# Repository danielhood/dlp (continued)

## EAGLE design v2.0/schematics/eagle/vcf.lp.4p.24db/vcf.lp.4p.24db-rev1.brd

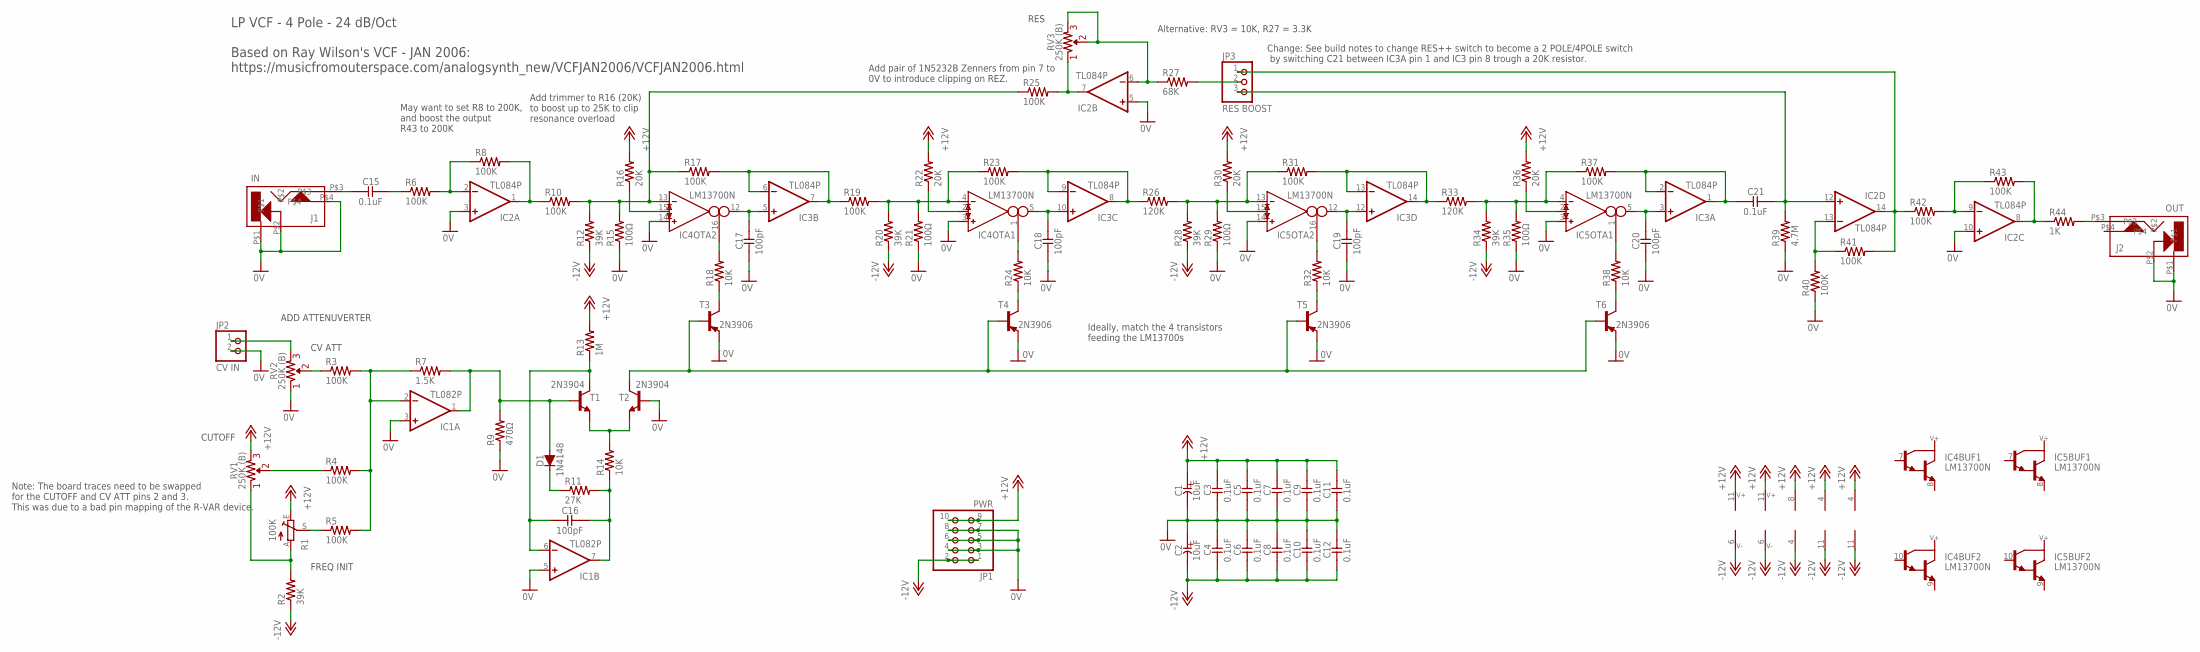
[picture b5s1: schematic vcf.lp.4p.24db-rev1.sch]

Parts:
C1, C2: 10uF; E2-5
C3, C4, C5, C6, C7, C8, C9, C10, C11, C12, C15, C21: 0.1uF; C025-024X044
C16, C17, C18, C19, C20: 100pF; C025-024X044
D1: 1N4148; DO35-7
IC1: TL082P; DIL08
IC2, IC3: TL084P; DIL14
IC4, IC5: LM13700N; DIL16
J1: IN; CL1384
J2: OUT; CL1384
JP1: PWR; 2X05
JP2: CV IN; 1X02
JP3: RES BOOST; 1X03
R1: 100K; CA6V
R2, R12, R20, R28, R34: 39K; 0207/7
R3, R4, R5, R6, R8, R10, R17, R19, R23, R25, R31, R37, R40, R41, R42, R43: 100K; 0207/7
R7: 1.5K; 0207/7
R9: 470Ω; 0207/7
R11: 27K; 0207/7
R13: 1M; 0207/7
R14, R18, R24, R32, R38: 10K; 0207/7
R15, R21, R29, R35: 100Ω; 0207/7
R16, R22, R30, R36: 20K; 0207/7
R26, R33: 120K; 0207/7
R27: 68K; 0207/7
R39: 4.7M; 0207/7
R44: 1K; 0207/7
RV1, RV2, RV3: 250K (B); _COMMON_3RP/1610N
T1, T2: 2N3904; TO92-EBC
T3, T4, T5, T6: 2N3906; TO92-EBC

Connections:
0V: C1.-, C2.+, C3.2, C4.1, C5.2, C6.1, C7.2, C8.1, C9.2, C10.1, C11.2, C12.1, C17.2, C18.2, C19.2, C20.2, IC1.3 (+IN), IC1.5 (+IN), IC2.3 (+IN), IC2.5 (+IN), IC2.10 (+IN), IC4.3 (IN_P), IC4.14 (IN_P), IC5.3 (IN_P), IC5.14 (IN_P), J1.P$1, J1.P$2, J1.P$4, J2.P$1, J2.P$2, JP1.3, JP1.4, JP1.5, JP1.6, JP1.7, JP1.8, JP2.2, R9.1, R15.1, R21.1, R29.1, R35.1, R39.1, R40.1, RV2.1, T2.B, T3.E, T4.E, T5.E, T6.E
+12V: C1.+, C3.1, C5.1, C7.1, C9.1, C11.1, IC1.8 (V+), IC2.4 (V+), IC3.4 (V+), IC4.11 (V+), IC5.11 (V+), JP1.9, JP1.10, R1.E, R13.2, R16.2, R22.2, R30.2, R36.2, RV1.2
-12V: C2.-, C4.2, C6.2, C8.2, C10.2, C12.2, IC1.4 (V-), IC2.11 (V-), IC3.11 (V-), IC4.6 (V-), IC5.6 (V-), JP1.1, JP1.2, R2.1, R12.1, R20.1, R28.1, R34.1
unnamed: R1.A, R2.2, RV1.1
unnamed: R4.1, RV1.3
unnamed: JP2.1, RV2.2
unnamed: R1.S, R5.1
unnamed: IC1.2 (-IN), R3.2, R4.2, R5.2, R7.1
unnamed: D1.A, IC1.1 (OUT), R7.2, R9.2, T1.B
unnamed: IC3.6 (-IN), IC3.7 (OUT), R17.2, R19.1
unnamed: R14.2, T1.E, T2.E
unnamed: C15.2, J1.P$3
unnamed: D1.C, R11.1
unnamed: C16.1, IC1.7 (OUT), R11.2, R14.1
unnamed: C16.2, IC1.6 (-IN), R13.1, T1.C
unnamed: R3.1, RV2.3
unnamed: T2.C, T3.B, T4.B, T5.B, T6.B
unnamed: IC4.1 (I_BIAS), R24.2
unnamed: R18.1, T3.C
unnamed: C17.1, IC3.5 (+IN), IC4.12 (OUT)
unnamed: IC4.16 (I_BIAS), R18.2
unnamed: IC4.15 (I_DIODE), R16.1
unnamed: IC4.4 (IN_N), R19.2, R20.2, R21.2, R23.1
unnamed: IC4.2 (I_DIODE), R22.1
unnamed: IC4.13 (IN_N), R10.2, R12.2, R15.2, R17.1, R25.1
unnamed: R24.1, T4.C
unnamed: C18.1, IC3.10 (+IN), IC4.5 (OUT)
unnamed: IC3.8 (OUT), IC3.9 (-IN), R23.2, R26.1
unnamed: IC5.13 (IN_N), R26.2, R28.2, R29.2, R31.1
unnamed: IC5.4 (IN_N), R33.2, R34.2, R35.2, R37.1
unnamed: IC5.15 (I_DIODE), R30.1
unnamed: IC3.13 (-IN), IC3.14 (OUT), R31.2, R33.1
unnamed: C19.1, IC3.12 (+IN), IC5.12 (OUT)
unnamed: IC5.16 (I_BIAS), R32.2
unnamed: R32.1, T5.C
unnamed: IC5.1 (I_BIAS), R38.2
unnamed: IC5.2 (I_DIODE), R36.1
unnamed: R38.1, T6.C
unnamed: C21.1, IC2.12 (+IN), JP3.3, R39.2
unnamed: JP3.2, R27.2
unnamed: C20.1, IC3.3 (+IN), IC5.5 (OUT)
unnamed: IC2.13 (-IN), R40.2, R41.1
unnamed: IC2.14 (OUT), JP3.1, R41.2, R42.1
unnamed: J2.P$3, R44.2
unnamed: IC2.1 (OUT), R8.2, R10.1
unnamed: IC2.2 (-IN), R6.2, R8.1
unnamed: IC2.7 (OUT), R25.2, RV3.1
unnamed: C15.1, R6.1
unnamed: IC2.6 (-IN), R27.1, RV3.2, RV3.3
unnamed: IC2.9 (-IN), R42.2, R43.1
unnamed: C21.2, IC3.1 (OUT), IC3.2 (-IN), R37.2
unnamed: IC2.8 (OUT), R43.2, R44.1

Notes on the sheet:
LP VCF - 4 Pole - 24 dB/Oct Based on Ray Wilson's VCF - JAN 2006: https://musicfromouterspace.com/analogsynth_new/VCFJAN2006/VCFJAN2006.html
CUTOFF
FREQ INIT
CV ATT
RES
ADD ATTENUVERTER
Add trimmer to R16 (20K) to boost up to 25K to clip resonance overload
Ideally, match the 4 transistors feeding the LM13700s
Note: The board traces need to be swapped for the CUTOFF and CV ATT pins 2 and 3. This was due to a bad pin mapping of the R-VAR device.
May want to set R8 to 200K, and boost the output R43 to 200K
Add pair of 1N5232B Zenners from pin 7 to 0V to introduce clipping on REZ.
Alternative: RV3 = 10K, R27 = 3.3K
Change: See build notes to change RES++ switch to become a 2 POLE/4POLE switch by switching C21 between IC3A pin 1 and IC3 pin 8 trough a 20K resistor.

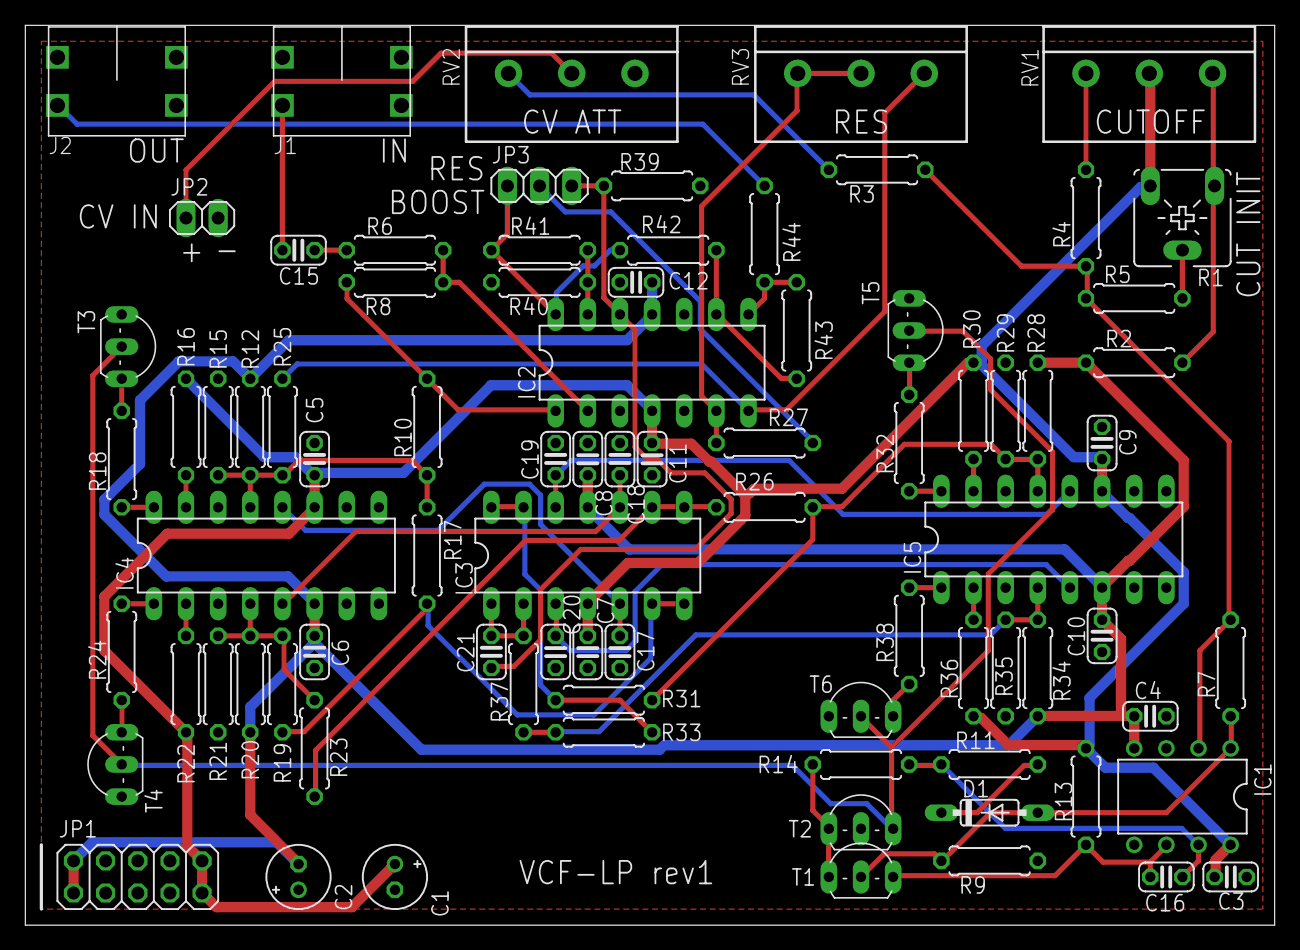
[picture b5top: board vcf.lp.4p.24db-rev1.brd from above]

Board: 2 copper layers, 98.7 x 71.1 mm, 83 parts (0 on the bottom side), 52 nets.

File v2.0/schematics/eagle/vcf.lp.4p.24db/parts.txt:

Partlist

Exported from vcf.lp.4p.24db-rev1.sch at 2024-02-20 09:59

EAGLE Version 9.6.2 Copyright (c) 1988-2020 Autodesk, Inc.

Assembly variant: 

Part     Value          Device              Package           Library             Sheet

C1       10uF           CE-USE2-5           E2-5              _common.v1          1
C2       10uF           CE-USE2-5           E2-5              _common.v1          1
C3       0.1uF          CC-US025-024X044    C025-024X044      _common.v1          1
C4       0.1uF          CC-US025-024X044    C025-024X044      _common.v1          1
C5       0.1uF          CC-US025-024X044    C025-024X044      _common.v1          1
C6       0.1uF          CC-US025-024X044    C025-024X044      _common.v1          1
C7       0.1uF          CC-US025-024X044    C025-024X044      _common.v1          1
C8       0.1uF          CC-US025-024X044    C025-024X044      _common.v1          1
C9       0.1uF          CC-US025-024X044    C025-024X044      _common.v1          1
C10      0.1uF          CC-US025-024X044    C025-024X044      _common.v1          1
C11      0.1uF          CC-US025-024X044    C025-024X044      _common.v1          1
C12      0.1uF          CC-US025-024X044    C025-024X044      _common.v1          1
C15      0.1uF          CC-US025-024X044    C025-024X044      _common.v1          1
C16      100pF          CC-US025-024X044    C025-024X044      _common.v1          1
C17      100pF          CC-US025-024X044    C025-024X044      _common.v1          1
C18      100pF          CC-US025-024X044    C025-024X044      _common.v1          1
C19      100pF          CC-US025-024X044    C025-024X044      _common.v1          1
C20      100pF          CC-US025-024X044    C025-024X044      _common.v1          1
C21      0.1uF          CC-US025-024X044    C025-024X044      _common.v1          1
D1       1N4148         1N4148              DO35-7            _common.v1          1
IC1      TL082P         TL082P              DIL08             linear              1
IC2      TL084P         TL084P              DIL14             linear              1
IC3      TL084P         TL084P              DIL14             linear              1
IC4      LM13700N       LM13700N            DIL16             ota                 1
IC5      LM13700N       LM13700N            DIL16             ota                 1
J1       IN             CL1384              CL1384            jacks               1
J2       OUT            CL1384              CL1384            jacks               1
JP1      PWR            PINHD-2X5           2X05              pinhead             1
JP2      CV IN          PINHD-1X2           1X02              pinhead             1
JP3      RES BOOST      PINHD-1X3           1X03              pinhead             1
R1       100K           TRIM_EU-CA6V        CA6V              pot                 1
R2       39K            R-US_0207/7         0207/7            resistor            1
R3       100K           R-US_0207/7         0207/7            resistor            1
R4       100K           R-US_0207/7         0207/7            resistor            1
R5       100K           R-US_0207/7         0207/7            resistor            1
R6       200K           R-US_0207/7         0207/7            resistor            1
R7       1.5K           R-US_0207/7         0207/7            resistor            1
R8       1M             R-US_0207/7         0207/7            resistor            1
R9       470?           R-US_0207/7         0207/7            resistor            1
R10      100K           R-US_0207/7         0207/7            resistor            1
R11      27K            R-US_0207/7         0207/7            resistor            1
R12      39K            R-US_0207/7         0207/7            resistor            1
R13      1M             R-US_0207/7         0207/7            resistor            1
R14      10K            R-US_0207/7         0207/7            resistor            1
R15      100?           R-US_0207/7         0207/7            resistor            1
R16      20K            R-US_0207/7         0207/7            resistor            1
R17      100K           R-US_0207/7         0207/7            resistor            1
R18      10K            R-US_0207/7         0207/7            resistor            1
R19      100K           R-US_0207/7         0207/7            resistor            1
R20      39K            R-US_0207/7         0207/7            resistor            1
R21      100?           R-US_0207/7         0207/7            resistor            1
R22      20K            R-US_0207/7         0207/7            resistor            1
R23      100K           R-US_0207/7         0207/7            resistor            1
R24      10K            R-US_0207/7         0207/7            resistor            1
R25      20K            R-US_0207/7         0207/7            resistor            1
R26      120K           R-US_0207/7         0207/7            resistor            1
R27      10K            R-US_0207/7         0207/7            resistor            1
R28      39K            R-US_0207/7         0207/7            resistor            1
R29      100?           R-US_0207/7         0207/7            resistor            1
R30      20K            R-US_0207/7         0207/7            resistor            1
R31      100K           R-US_0207/7         0207/7            resistor            1
R32      10K            R-US_0207/7         0207/7            resistor            1
R33      120K           R-US_0207/7         0207/7            resistor            1
R34      39K            R-US_0207/7         0207/7            resistor            1
R35      100?           R-US_0207/7         0207/7            resistor            1
R36      20K            R-US_0207/7         0207/7            resistor            1
R37      100K           R-US_0207/7         0207/7            resistor            1
R38      10K            R-US_0207/7         0207/7            resistor            1
R39      4.7M           R-US_0207/7         0207/7            resistor            1
R40      100K           R-US_0207/7         0207/7            resistor            1
R41      100K           R-US_0207/7         0207/7            resistor            1
R42      100K           R-US_0207/7         0207/7            resistor            1
R43      100K           R-US_0207/7         0207/7            resistor            1
R44      1K             R-US_0207/7         0207/7            resistor            1
RV1      250K (B)       R-VARR-VAR-10       _COMMON_3RP/1610N _common             1
RV2      250K (A)       R-VARR-VAR-10       _COMMON_3RP/1610N _common             1
RV3      10K (B)        R-VARR-VAR-10       _COMMON_3RP/1610N _common             1
T1       2N3904         2N3904-NPN-TO92-EBC TO92-EBC          transistor-neu-to92 1
T2       2N3904         2N3904-NPN-TO92-EBC TO92-EBC          transistor-neu-to92 1
T3       2N3906         2N3906-PNP-TO92-EBC TO92-EBC          transistor-neu-to92 1
T4       2N3906         2N3906-PNP-TO92-EBC TO92-EBC          transistor-neu-to92 1
T5       2N3906         2N3906-PNP-TO92-EBC TO92-EBC          transistor-neu-to92 1
T6       2N3906         2N3906-PNP-TO92-EBC TO92-EBC          transistor-neu-to92 1

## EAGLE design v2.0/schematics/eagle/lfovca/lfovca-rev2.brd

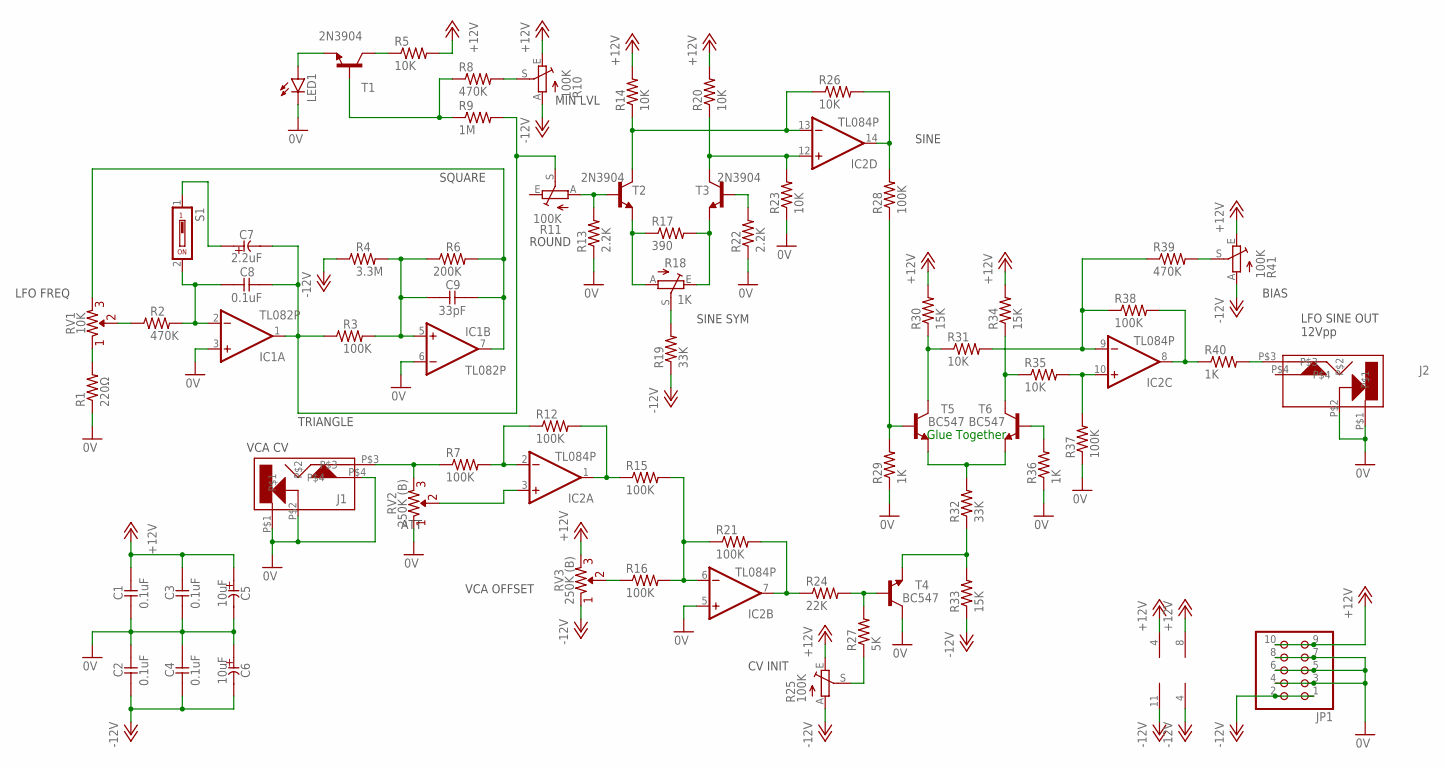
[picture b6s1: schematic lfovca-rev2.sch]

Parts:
C1, C2, C3, C4, C8: 0.1uF; C025-024X044
C5, C6: 10uF; E2-5
C7: 2.2uF; E2-5
C9: 33pF; C025-024X044
IC1: TL082P; DIL08
IC2: TL084P; DIL14
J1, J2: CL1384
JP1: PINHD-2X5; 2X05
LED1: LED3MM
R1: 220Ω; 0207/7
R2, R8, R39: 470K; 0207/7
R3, R7, R12, R15, R16, R21, R28, R37, R38: 100K; 0207/7
R4: 3.3M; 0207/7
R5, R14, R20, R23, R26, R31, R35: 10K; 0207/7
R6: 200K; 0207/7
R9: 1M; 0207/7
R10, R11, R25, R41: 100K; CA6V
R13, R22: 2.2K; 0207/7
R17: 390; 0207/7
R18: 1K; CA6V
R19, R32: 33K; 0207/7
R24: 22K; 0207/7
R27: 5K; 0207/7
R29, R36, R40: 1K; 0207/7
R30, R33, R34: 15K; 0207/7
RV1: 10K; _COMMON_3RP/1610N
RV2, RV3: 250K (B); _COMMON_3RP/1610N
S1: DS01; DS-01
T1, T2, T3: 2N3904; TO92-EBC
T4, T5, T6: BC547; TO92-CBE

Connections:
0V: C1.2, C2.1, C3.2, C4.1, C5.-, C6.+, IC1.3 (+IN), IC1.6 (-IN), IC2.5 (+IN), J1.P$1, J1.P$2, J1.P$4, J2.P$1, J2.P$2, JP1.3, JP1.4, JP1.5, JP1.6, JP1.7, JP1.8, LED1.K (C), R1.1, R13.1, R22.1, R23.1, R29.1, R36.1, R37.1, RV2.1, T4.C
+12V: C1.1, C3.1, C5.+, IC1.8 (V+), IC2.4 (V+), JP1.9, JP1.10, R5.2, R10.E, R14.2, R20.2, R25.E, R30.2, R34.2, R41.E, RV3.2
-12V: C2.2, C4.2, C6.-, IC1.4 (V-), IC2.11 (V-), JP1.1, JP1.2, R4.1, R10.A, R19.1, R25.A, R33.1, R41.A, RV3.1
unnamed: R16.1, RV3.3
unnamed: IC2.7 (OUT), R21.2, R24.1
unnamed: IC2.3 (+IN), RV2.3
unnamed: R25.S, R27.1
unnamed: R24.2, R27.2, T4.B
unnamed: IC2.6 (-IN), R15.2, R16.2, R21.1
unnamed: IC2.9 (-IN), R31.2, R38.1, R39.1
unnamed: C8.2, IC1.2 (-IN), R2.2, S1.2
unnamed: C7.-, C8.1, IC1.1 (OUT), R3.1, R9.2, R11.S
unnamed: R30.1, R31.1, T5.C
unnamed: R34.1, R35.1, T6.C
unnamed: C9.2, IC1.5 (+IN), R3.2, R4.2, R6.1
unnamed: C9.1, IC1.7 (OUT), R6.2, RV1.2
unnamed: IC2.10 (+IN), R35.2, R37.2
unnamed: R32.1, R33.2, T4.E
unnamed: R2.1, RV1.3
unnamed: R1.2, RV1.1
unnamed: R32.2, T5.E, T6.E
unnamed: R28.1, R29.2, T5.B
unnamed: IC2.8 (OUT), R38.2, R40.1
unnamed: J2.P$3, R40.2
unnamed: IC2.2 (-IN), R7.2, R12.1
unnamed: IC2.1 (OUT), R12.2, R15.1
unnamed: J1.P$3, R7.1, RV2.2
unnamed: R36.2, T6.B
unnamed: IC2.14 (OUT), R26.2, R28.2
unnamed: IC2.12 (+IN), R20.1, R23.2, T3.C
unnamed: IC2.13 (-IN), R14.1, R26.1, T2.C
unnamed: R22.2, T3.B
unnamed: R17.1, R18.A, T2.E
unnamed: R17.2, R18.E, T3.E
unnamed: R11.A, R13.2, T2.B
unnamed: R18.S, R19.2
unnamed: R8.2, R10.S
unnamed: R5.1, T1.C
unnamed: R8.1, R9.1, T1.B
unnamed: LED1.A, T1.E
unnamed: C7.+, S1.1
unnamed: R39.2, R41.S

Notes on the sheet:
VCA CV
VCA OFFSET
LFO SINE OUT 12Vpp
LFO FREQ
ATT
CV INIT
SINE
TRIANGLE
SQUARE
BIAS
MIN LVL
SINE SYM
ROUND
Glue Together

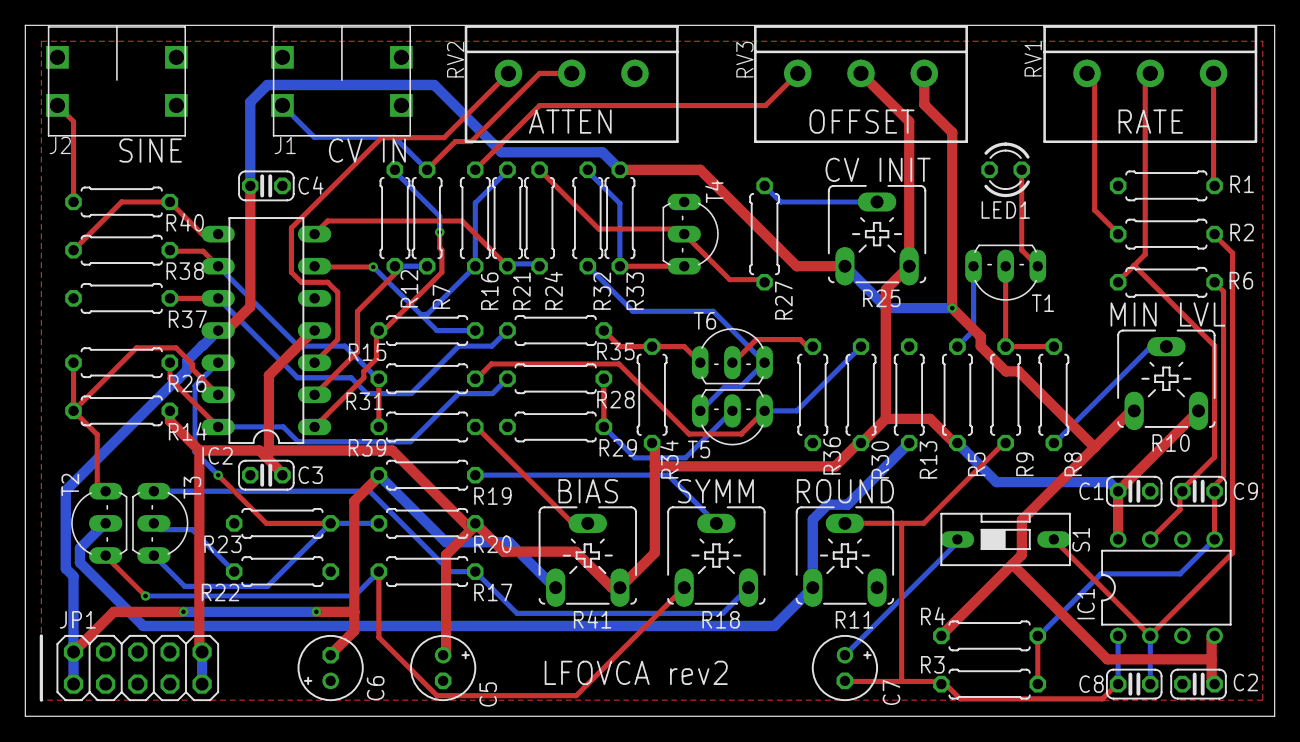
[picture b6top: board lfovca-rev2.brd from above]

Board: 2 copper layers, 98.7 x 54.6 mm, 66 parts (0 on the bottom side), 42 nets.

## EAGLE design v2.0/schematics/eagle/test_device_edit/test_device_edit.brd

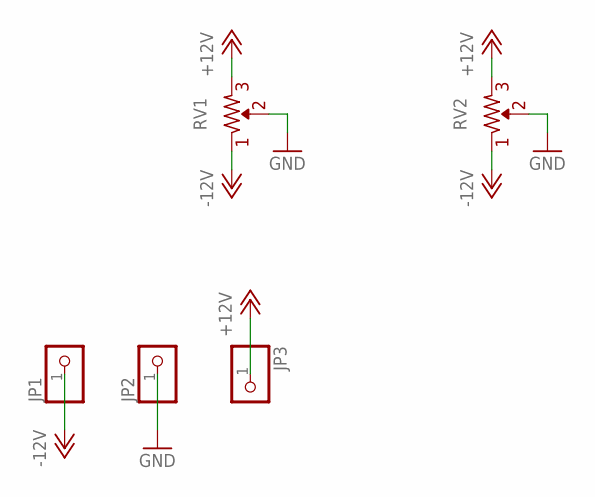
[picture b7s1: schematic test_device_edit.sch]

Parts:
JP1, JP2, JP3: PINHD-1X1; 1X01
RV1: R-VAR
RV2: R-VARR-VAR-10; _COMMON_3RP/1610N

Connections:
+12V: JP3.1, RV1.R2 (3), RV2.3
-12V: JP1.1, RV1.R1 (1), RV2.1
GND: JP2.1, RV1.VAR (2), RV2.2

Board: 2 copper layers, 5 parts (0 on the bottom side), 3 nets, no tracks yet.

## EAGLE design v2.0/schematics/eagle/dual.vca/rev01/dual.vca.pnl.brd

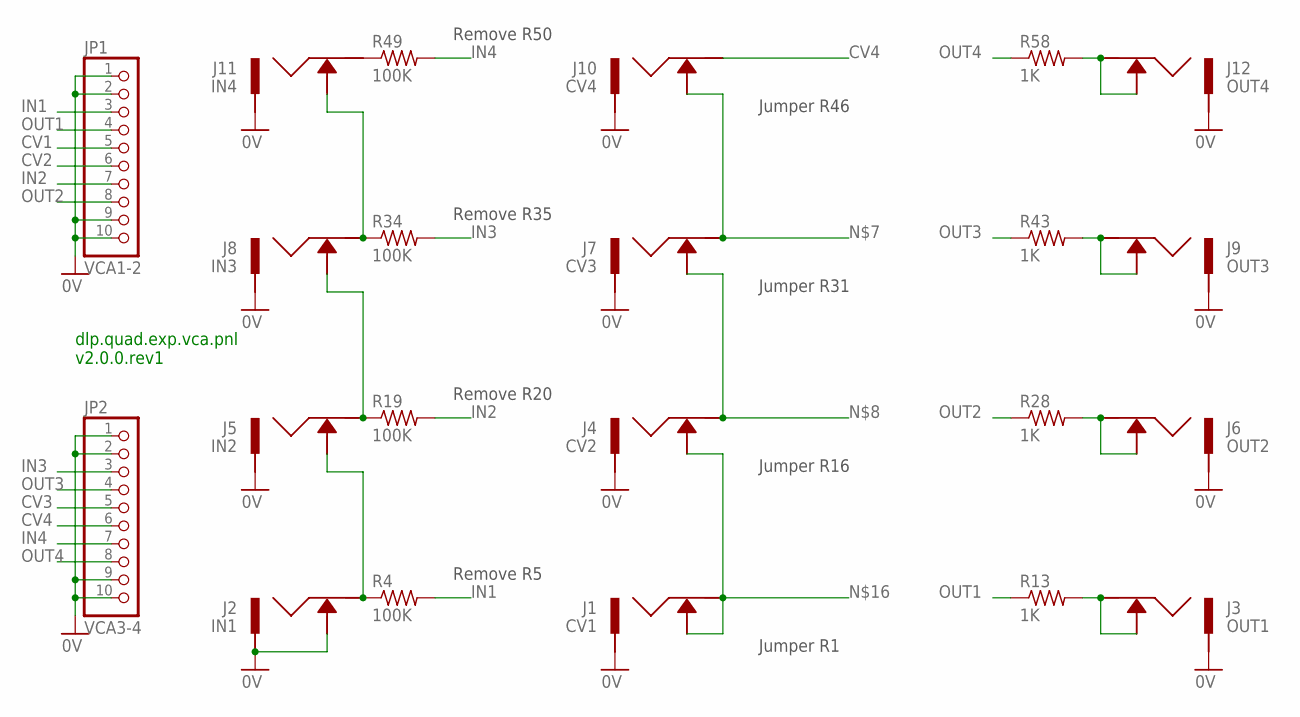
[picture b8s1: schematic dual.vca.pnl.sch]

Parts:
J1: CV1; ACJM-MV35-2S
J2: IN1; ACJM-MV35-2S
J3: OUT1; ACJM-MV35-2S
J4: CV2; ACJM-MV35-2S
J5: IN2; ACJM-MV35-2S
J6: OUT2; ACJM-MV35-2S
J7: CV3; ACJM-MV35-2S
J8: IN3; ACJM-MV35-2S
J9: OUT3; ACJM-MV35-2S
J10: CV4; ACJM-MV35-2S
J11: IN4; ACJM-MV35-2S
J12: OUT4; ACJM-MV35-2S
JP1: VCA1-2; 1X10
JP2: VCA3-4; 1X10
R4, R19, R34, R49: 100K; 0207/7
R13, R28, R43, R58: 1K; 0207/7

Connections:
0V: J1.P$1, J2.P$1, J2.P$2, J3.P$1, J4.P$1, J5.P$1, J6.P$1, J7.P$1, J8.P$1, J9.P$1, J10.P$1, J11.P$1, J12.P$1, JP1.1, JP1.2, JP1.9, JP1.10, JP2.1, JP2.2, JP2.9, JP2.10
CV1: JP1.5
CV2: JP1.6
CV3: JP2.5
CV4: J10.P$3, JP2.6
IN1: JP1.3, R4.2
IN2: JP1.7, R19.2
IN3: JP2.3, R34.2
IN4: JP2.7, R49.2
unnamed: J9.P$2, J9.P$3, R43.2
unnamed: J3.P$2, J3.P$3, R13.2
unnamed: J2.P$3, J5.P$2, R4.1
unnamed: J5.P$3, J8.P$2, R19.1
unnamed: J8.P$3, J11.P$2, R34.1
unnamed: J7.P$3, J10.P$2
unnamed: J4.P$3, J7.P$2
unnamed: J1.P$2, J1.P$3, J4.P$2
unnamed: J6.P$2, J6.P$3, R28.2
unnamed: J12.P$2, J12.P$3, R58.2
unnamed: J11.P$3, R49.1
OUT1: JP1.4, R13.1
OUT2: JP1.8, R28.1
OUT3: JP2.4, R43.1
OUT4: JP2.8, R58.1

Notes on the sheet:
dlp.quad.exp.vca.pnl v2.0.0.rev1
Remove R50
Remove R35
Remove R20
Remove R5
Jumper R46
Jumper R31
Jumper R16
Jumper R1

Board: 2 copper layers, 22 parts (2 on the bottom side), 21 nets, no tracks yet.

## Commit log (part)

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2012-03-30 inital creation
2012-03-30 Added pic CV assembly project and VCO schematics
2012-03-30 Changed PWM on OSC1. Added PWM Knob to OSC2 Updated resistor value on OSC1 SQ wave.
2012-03-30 Added 2 channel mixer schematic.
2013-10-30 Added ADSR envelope generator.
2013-11-03 Added schematic for MIDI to CV Converter Updated common library.
2013-11-03 Added png exports
2013-11-07 Updated VCA schem. Added VCF Diode Ladder
2013-11-08 Updated vco with correct pot values Updated vcf with new values and added in manual CV control.
2013-11-08 updated vcf resonance amp r val
2013-11-11 Added dual version of ASDR Added PSU schem Updated VCF
2013-11-17 Updated ASDR with revised values
2013-11-17 Refreshed ASDR pdf (removed png) Updated VCO values Added Pitch Link to VCO Replaced OSC2 LOG.FM with LIN.FM Updated PDF (removed png)
2013-11-17 Added VCO pdf
2013-11-20 Updated ASDR with 200K Log pots for decay
2013-11-22 Added LM13700 to common library. Added start of LFO schem (based on VCO). Still need to prototype and set proper values.
2013-11-26 Updated VCO with revised values and added bypass capacitors
2013-11-29 Added v2.0 of the midi2cv controller program, however incomplete. The PIC18F2431 cannot have more than 3 independent PWM outs, preventing us from implementing the 2nd PITCH/VEL/MOD chanel.
2013-11-29 Created v3 (drum triggers) for midi2cv
2013-11-30 Updated label on VEL2
2013-11-30 Update v3 with new multi-mode def's Implemented MODE0 (MODE1 still to come)
2013-12-01 Correction to code after testing. Verified MODE0 works.
2013-12-01 Completed implmentation and testing of MODE1
2013-12-11 Added candidate schem for 909 BD
2015-04-25 Added inital v2.0 folder with copy of vco
2015-04-25 Added files
2015-04-26 Created simplified single version of VCO
2015-04-26 Added header version of vco Added first attempt at board
2015-04-27 Added inital board for main schem (no real layout applied)
2015-04-27 A bunch of old change from midi.cv 3.0
2015-04-27 Initial optimzation of main board (bad layout)
2015-04-28 Autoroute main board v1.1.2
2015-04-28 Generated gerber for main board v1.1.2
2015-04-28 Added zip of gerber for submission
2015-04-29 Added vco.1.1.3 (removed dual osc name as this is now just a single osc board) Removed 1M trim and fixed at 220M
2015-04-29 Added notes for working replacement for NTE912
2015-04-29 Repalced NTE912 with 2N4401 Added 2N4401 to _common.lbr
2015-04-29 Condensed 1.1.3 and generated checked route
2015-04-30 Updated values for fixed PWM2
2015-04-30 Minort schem layout edits
2015-05-13 Expoted BOM
2015-06-13 Split EXP1 and 2 and added EXP2 IN Removed PWM1 ATT and added PWM2
2015-06-13 Created pannel board and inital layout Updated common libraries for pannel layout and pin tracking
2015-06-14 Reduced size of vco pannel and applied routing
2015-06-17 Created inital schem for Quad Decay/VCA board
2015-06-21 Changed 10K to 390 on vca schem
2016-02-01 Generated Gerbrer files submitted to Seeed for OSC panel
2016-02-05 Added revised schems and board layout for midi2cv module
2016-02-08 Opened midi2cv.rev2 to eliminate link to 0V on switchd outs
2016-03-01 Corrected pin mappings on Jacks Updated midi2cv with new jacks mapping Rerouted main and pnl Increased minimum width in design rules from 6mil to 12mil
2016-03-02 Added v2.0 of midi.cv pic firmare
2016-03-02 Roated midi jack
2016-03-02 Updated version on schem and board to 2.2 Revised labels for GATE1..5 to match board layout and firmare
2016-03-02 Added design for basic front panel layout
2016-03-04 Added inital schem and board for quad.vca module. Added ota library for LM137000 Modified symbol for switched mono jacks Added 2N3904 and 7.5mm resistor to common.lbr
2016-03-17 Added front panel for vco
2016-03-18 Moved jacks on vco to accomodate width of plugs
2016-03-19 Created quad.exp.vca schem and front panel. Renamed previous quad panel to dual.
2016-03-19 renumber parts
2016-03-19 Split quad.exp.vca into main and pnl boards with completed autorouting
2016-03-19 Rotated power jack
2016-03-19 Added gerber files for quad.exp.vca
2016-03-25 Modified Synth mode (MODE0) to respect MIDI chan's 1, 2, 3 and only track pitch on each
2016-03-26 Added support for gates on CH4 and 5 in MODE0 Corrected channel mappings
2016-03-26 Inital add of digital.noise.gen module (part of Percussion Voice VCF Mod module)
2016-03-27 Added .NET console app to test 8bit PRNG alg
2016-03-28 Added xorgen function to pic noise gen code
2016-03-31 Updated resistor values on quad vca
2017-01-16 Added system holes for vco 1.1.4 panel
2017-02-04 Created v1.0.1 of quad decay with tested values
2017-02-04 Created jack package for CL1384
2017-02-09 Added EOC on quad decay with tested values Added Zenner diode to _common.lbr
2017-02-09 Duplicated main schem (x4)
2017-02-09 Completed layout of main board for quad decay
2017-02-10 Added panel board for quad decay and routed main and pnl
2017-02-10 Updated routing and jack position.
2017-02-11 Added front panel design for quad decay
2017-02-12 Added copy of midi2cv code to establish midi.clock
2017-02-13 Added wav generator and sine lfo on PITCH over quarter note
2017-02-13 Fixed compile for Sine LFO on CV1
2017-02-14 Added build script for gpasm Added 96 and 32 stepped sine tables
2017-02-14 Fixes for sine outs
2017-02-15 Generated gerber files for quad decay boards for Seeed order
2017-02-19 Renamed dcy.vca v1.0.1 to quad.decay Removed library backup files
2017-02-20 Inital schem for Dual Sequencer
2017-02-21 Finalized all i/o channels on dual.seq
2017-02-25 Dual seq panel schem
2017-02-25 Added board for dual seq panel
2017-02-25 Added boards for dual seq main and pnl
2017-02-28 Inital routing for main pnl (too many vias)
2017-02-28 Upated layout and routing for dual.seq main board
2017-02-28 Route for dual.seq pnl
2017-04-03 Added v1.0.2 to correct pwr on LM324 and restor value updates
2017-06-06 Added gerber files for dual.seq
2017-06-18 Added front panel for dual seq
2017-06-18 Updated spacing and labels for dual.seq front panel
2017-06-18 dual.seq rev 1.0.1 for layout adjustments for main board
2017-06-19 Added note on inverted header to dual.seq pnl
2017-06-19 Initial code for dual.seq to test gate and cv outs and clock and button ins
2017-06-21 Added note to move pot on main board 2mm
2017-06-21 Support for LEDs, target selection, added set button, and button debouncing
2017-11-05 Fixed timing on gate outs for MIDI Clock module
2017-11-12 Add song start/stop support to MIDI clock
2017-11-13 Setup A/D conversion in dual seq
2017-11-14 Added sequencing for CV outs
2017-11-14 Fixed A/D scaling for CV
2018-01-28 Added dxf and pdf exports of Dual Seq panel
2018-02-22 Added clk.div project (copy from dual.seq)
2018-02-22 Project cleanup
2018-05-23 Remvoed unecessary check for DIR1/DIR2 as possible cause for random shuffle/sawp
2018-05-30 Prevent interrupts from corrupting stack in clk.div
2018-08-21 Attempt to stablize clock adding save/restore registers on interrupts and reduce frequency of analog sampling
2018-08-22 Store registers on interrupt Use 8bit instead of 16bit vars Reduce frequency of TMR5 triggering of AD conversion sampling
2018-08-22 Added state check to dual.seq set button for note on
2019-02-02 Added support for variable gate length on SEQ 2 and 3
2019-02-02 DIR1 now controls direction on all patterns
2019-02-08 Added BOM for dual.seq
2019-02-22 Initial add of func.gen project
2019-02-23 Simple LFO with rate set from LVL
2019-02-23 Param select
2019-02-23 Added clock trigger/reset
2019-02-23 Triangles on all 3 channels
2019-02-23 CV and GATE (slope) out from triangle
2019-02-23 Added in offsets from CV params
2019-02-24 Added A/D conv for inputs. Note mappings are incorrect.
2019-02-27 Remapped CV params; added offest to reset
2019-03-14 Added good build of synth/drum mode
2019-03-14 Prevent clearing CV's for drum mode for noteoff
2019-03-14 Detach velocity from cv outs in drum mode
2019-03-16 Added preset mode to dual.seq
2019-03-16 Updated defaults for dual.seq
2019-03-16 Updated defaults for clock.div
2019-03-24 Created midi.clockgen from copy of midi.cv
2019-03-24 Created midi.clockgen from copy of midi.clock
2019-03-24 Gutted code and added manual loop to test CV/GATES
2019-03-24 Working start/stop and clock TX
2019-03-25 Run Timer1 with 1:2 prescaler; start/stop clock with button
2019-03-25 Update GATE clocks with Timer1 trigger
2019-03-26 Fixed clockgen CVs; debounced start/stop button
2019-03-26 Lengthened CV periods
2019-04-14 Move reset signal sooner on button push
2019-04-14 Ensure clocks and reset are low on song stop
2019-04-14 builds
2020-07-11 clk.div: in phase reset
2020-07-11 Compile errors; Force outs on reset
2021-01-26 Added new dual.vca project based on http://yusynth.net
2021-02-02 Swaped Transitors for BC547C; swaped to 100K trim
2021-02-04 Project mods
2021-02-11 Added comparator to dual.vca
2021-07-17 Cloned clk.div to clk.div-gen
2021-07-17 Inverted outputs to have hi freq at stable gate jacks
2021-09-21 Added mono.stereo.mixer
2021-09-22 Added mono.stereo.mix panel and build notes
2021-11-06 Iniital board layout for main dual.vca
2021-11-06 Dual VCA autoroute and ground planes
2021-11-07 Dual VCA jumper board ground planes and autoroute
2021-11-07 Add protoboard to eagle project
2021-11-08 Adjusted Dual.Seq comparrator
2021-12-06 Final board cams
2021-12-06 Added cam files; annotate panel schem with board edits; update cv resistor values
2021-12-13 Added panel underlays
2021-12-18 Updated dual.vca panel from 16hp to 18hp
2021-12-19 Finalized dual.vca panel in svg format
2023-03-21 Inital add of LFOVCA
2023-03-22 Updated values for LFOVCA
2023-03-26 Added LFOVCA rev2: removes lm13700
2023-03-26 LFOVCA value and bias connection changes
2024-02-14 Added board for LFOVCA
2024-02-16 LFOVCA: Optimize routes; cam outputs
2024-02-16 Update eagle file for LFOVCA
2024-02-17 LFOVCA board and panel revisions
2024-02-18 Added pannel for protoboard
2024-02-18 Added initial schem for VCF-LP
2024-02-18 VFC-LP: schem renum; power pins; erc approve
2024-02-20 VCF-LP: Removed CV RES; Updated values from test build
2024-02-20 VCF-LF: Schem cleanup for removed ICs; update panel
2024-02-21 Panel revisions; VCF-LP board layout
2024-03-06 Added note for VCF attenuverter
2024-03-06 Updated LFO panel for attenuverter scale
2024-03-10 Updatd values for VCFLP
2024-03-16 VCFLP - added build notes and updated parts list
2024-03-16 VCFLP - updaed schem note
2024-03-17 VCFLP - Updated notes to support Zenner clipping on RES.
2024-03-19 VCFLP - Updated in/out resistors; updated notes on zenner rez clipping
2024-03-23 Corrected R-VAR pin 2 & 3 mapping for VCFLP and LFOVCA
2024-03-23 VCFLP - updated rev3 with zenner clipping
2024-03-23 LFOVCA - moved value attributes
2024-03-24 VCFLP/LFOVCA: Updated build notes
2024-03-24 VCFLP: Updated build notes
2024-03-24 VCFLP/LFOVCA: Corrected build notes
2024-10-15 Updated build notes
2025-05-11 midi2cv tuning
2025-05-11 midi2cv: fix ch 2 & 3 scaling in synth mode
2025-05-11 midi2cv: additional tuning
2025-05-11 midi2cv: build with final tuning
2026-03-29 Added inital mixer schems
2026-03-30 Added input stage to mixer
2026-04-03 Updated caps to 100uF
2026-04-03 Added stereo line in; output level
2026-04-05 Added DRV134 for output stage
2026-04-05 Added output meter
2026-04-05 Completed initial mixer schematic draft
2026-04-09 Fixed jack grounds; normalled R to L; increased master gain
2026-04-11 Updated VAR-ST; Added FX Crossfades; Ran error checks
2026-04-11 Updated cap packages
2026-04-13 Chnaged 3.3nF filter caps to poly film device layout:
2026-04-13 Mixer board 1 layout
2026-04-13 Route mixer board 1
2026-04-13 Ground plane
2026-04-14 Mixer Board 2 layout
2026-04-14 Route Mixer Board 2
2026-04-14 Mixer Board 3 layout
2026-04-14 Mixer board 3 route and ground plane
2026-04-14 Mixer Board 4 layout
2026-04-15 Added mixer panel
2026-04-15 Updated mixer panel; added exports
2026-04-15 Mixer gerber files
2026-04-18 Updated mixer board 4 with meter build adjustments
2026-05-10 Updated board notes
2026-05-10 Desktop screen res
